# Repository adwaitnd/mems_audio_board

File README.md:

# MEMS Audio Board
Audio board for connecting a MEMS microphone to professional audio equipment through an unbalanced input line

## Important To-Do's

- Micrel voltage regulator no longer available. Use suitable alternative in design
- Switch to standard 3.5 mm jack

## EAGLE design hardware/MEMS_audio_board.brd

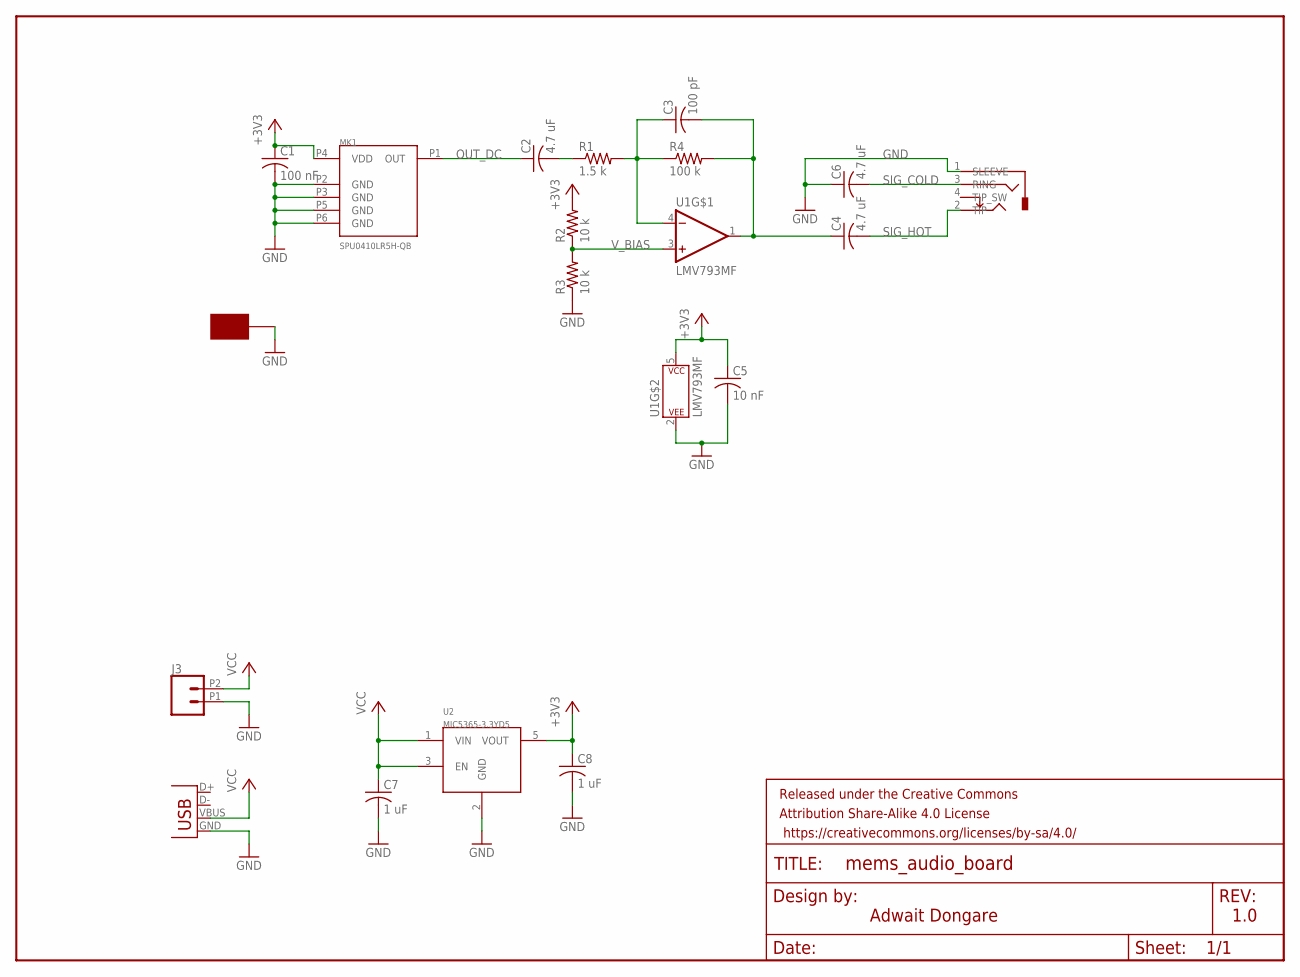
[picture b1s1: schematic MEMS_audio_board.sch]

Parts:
C1: 100 nF; C0603
C2, C4, C6: 4.7 uF; C0603
C3: 100 pF; C0603
C5: 10 nF; C0603
C7, C8: 1 uF; C0603
FRAME1: FRAME-LETTERNO_PACKAGE; DUMMY
J1: SJ-2524-SMT
J2: USBSMD; USB-MINIB
J3: CONN_022.54MM_SCREWTERM; 1X02_2.54_SCREWTERM
MK1: SPU0410LR5H-QB
R1: 1.5 k; R0603
R2, R3: 10 k; R0603
R4: 100 k; R0603
TP: TEST_PAD-0.4X0.1; TESTPAD_10.16X2.54
U1: LMV793MF; SOT23-5
U2: MIC5365-3.3YD5; SOT23-5

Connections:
+3V3: C1.1, C5.1, C8.1, MK1.P4 (VDD), R2.2, U1.5 (P$V+), U2.5 (VOUT)
GND: C1.2, C5.2, C6.1, C7.2, C8.2, J1.1 (SLEEVE), J2.GND, J3.P1 (1), MK1.P2 (GND), MK1.P3 (GND), MK1.P5 (GND), MK1.P6 (GND), R3.1, TP.P$1, U1.2 (P$V-), U2.2 (GND)
unnamed: C3.1, R1.2, R4.1, U1.4 (-IN)
unnamed: C3.2, C4.1, R4.2, U1.1 (OUT)
OUT_AC: C2.2, R1.1
OUT_DC: C2.1, MK1.P1 (OUT)
SIG_COLD: C6.2, J1.3 (RING)
SIG_HOT: C4.2, J1.2 (TIP)
VCC: C7.1, J2.VBUS, J3.P2 (2), U2.1 (VIN), U2.3 (EN)
V_BIAS: R2.1, R3.2, U1.3 (+IN)

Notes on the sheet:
Adwait Dongare
1.0

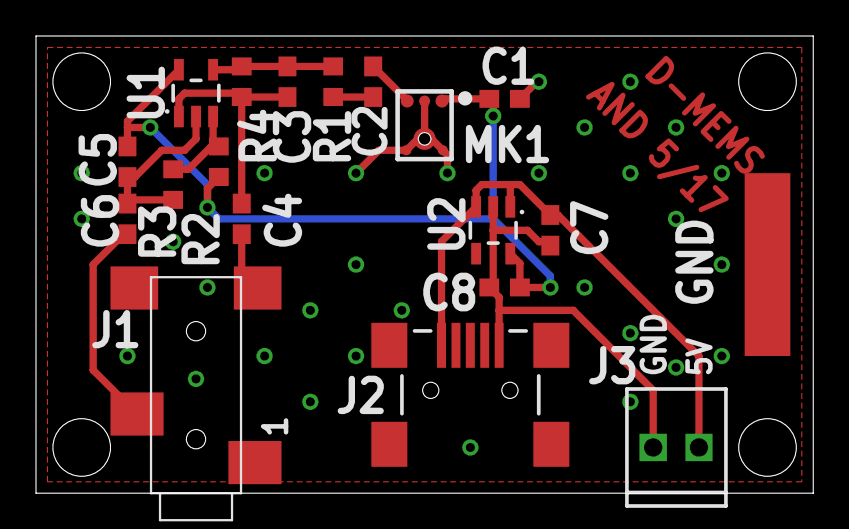
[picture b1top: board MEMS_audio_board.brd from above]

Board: 2 copper layers, 43.2 x 25.4 mm, 20 parts (0 on the bottom side), 10 nets.

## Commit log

2017-05-20 updated files
2017-05-25 corrected flipped mic layout

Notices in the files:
parts and their libraries:
SparkFun-Aesthetics: Licensing: Creative Commons ShareAlike 4.0 International - https://creativecommons.org/licenses/by-sa/4.0
SparkFun: Licensing: CC v3.0 Share-Alike You are welcome to use this library for commercial purposes.
SparkFun-Aesthetics: https://creativecommons.org/licenses/by-sa/4.0
